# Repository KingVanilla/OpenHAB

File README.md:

# OpenHAB
This repository contains configuration files for my OpenHAB2 home automation system.

Included in this repository are details about my custom alarm system which integrates the ESP32/ESP8266 chipset with OpenHAB.  Included information contains all hardware and software schematics.

## How it all works
My family has several [Bravo5 motion detectors](http://www.dsc.com/alarm-security-products/BV-500GB,%20BV-501GB,%20BV-502GB%20-%20Bravo%C2%AE%205%20360%C2%B0%20Ceiling-Mount%20PIR%20Motion%20Detectors/76) in our home which were prevoisly interfaced with a standard unmonitored alarm system.  4-conductor cabling was ran from each sensor to the control board as well as to 2 keypads on the main and second floor of our home.  The 4-conductor cable delivers 12V to each sensor with a pair of wires.  The remaining pair of wires is connected to the internal relay contact of the motion sensor which are electrically connected by the relay when motion is detected.  I have these sensors interfaced with my ESP8266 via optocouplers so that the 12V signal from the sensor does not fry the ESP which operates on 3.3V.  To replace the 2 keypads in our home I opted to use Amazon Fire tablets and HABPanel.  This solution proves cost-effective, simple to impliment, and elegant.  I used to 4-conductor cable going to these locations to pass 12V to these [USB charging adapters](https://smile.amazon.com/gp/product/B07121W7Q4/ref=oh_aui_search_detailpage?ie=UTF8&psc=1) to keep the tablets supplied with a charge.  I followed [this guide on YouTube](https://www.youtube.com/watch?v=DBfwKYFbbb8) to get the tablets running the HABPanel interface.  Beware, however, that Fire tablets don't allow you to unlock them via Tasker which basically means that you can't have the tablets automatically lock and unlock when there's motion.  I just have mine setup so that the screen is contantly on and never locks. The system logic occurs on the OpenHAB side, so the ESP8266 is simply reporting motion to OpenHAB and receiving commands when to trigger the siren relay.  Connected to the siren relay is this [Elk siren driver board](https://www.homecontrols.com/ELK-Two-Channel-Siren-Driver-Module-ELK101) which has a "chirp" and "constant" tone setting.

## HABPanel
- The passcode input is interfaced though the "Universal Keypad widget" which I have linked to the alarmKeypadInput item 
- Several "Attention with Button" widgets display the alarm status and zone status for each sensor.  
- "Selection" widiget with "Arm=Arm,Chime=Chime,Triggered=Manual Trip" as my list of comma-separated choices to control the alarm mode
- Button to control the lights on the main level of my home
- Button and "Attention with Button" to control and display the status of my garage  

## My PCB design files
The PCB files in this repository feature a board which can interface with up to 4 motion sensors and 1 relay.  The board takes a 12V 5A power supply via a standard DC power-jack.  The design features 4 M3 mounting holes, 1 power LED connected to the 3.3V line, 1 LED connected to D5, and a screw-terminal connected to 12V which I have used to connect to the 4-conductor cabling to run power to the tablets.  You can, obviously, modify the design to meet your own specifications.

## BOM for PCB (links to DigiKey and AmazonSmile)
For the PCB itself you will need:
 - [1x DC Jack](https://www.digikey.com/product-detail/en/cui-inc/PJ-102AH/CP-102AH-ND/408448)
 - [Non-stackable female headers](https://smile.amazon.com/Straight-Female-Header-Spacing-Connector/dp/B00TGOJE1W/ref=sr_1_7?ie=UTF8&qid=1528657475&sr=8-7&keywords=female+headers)
 - [1x ESP8266](https://smile.amazon.com/HiLetgo-Internet-Development-Wireless-Micropython/dp/B010O1G1ES/ref=sr_1_1_sspa?s=electronics&ie=UTF8&qid=1528657504&sr=1-1-spons&keywords=esp8266&psc=1)
 - [1x 2-pin 3.5mm screw terminal](https://www.digikey.com/product-detail/en/phoenix-contact/1984617/277-1721-ND/950849)
 - [1x 12V to 5V regulator](https://smile.amazon.com/DROK-Regulator-Converter-Step-down-Transformer/dp/B0758ZTS61/ref=sr_1_10?ie=UTF8&qid=1528657574&sr=8-10&keywords=12v+to+5v+converter)
 - [2x 68 ohm 0603 resistors](https://www.digikey.com/product-detail/en/rohm-semiconductor/ESR03EZPJ270/RHM27DCT-ND/4053754)
 - [2x 0805 leds](https://www.digikey.com/product-detail/en/lite-on-inc/LTST-C170KFKT/160-1413-1-ND/386774)

For each sensor you wish to interface with you will need:
 - [1x PCB screw terminal connector](https://smile.amazon.com/gp/product/B01M5FARN8/ref=oh_aui_search_detailpage?ie=UTF8&psc=1)
 - [1x PC817 optocoupler](https://smile.amazon.com/gp/product/B06X6M2NNY/ref=oh_aui_search_detailpage?ie=UTF8&psc=1)
 - [1x 0603 10k ohm resistor](https://www.digikey.com/product-detail/en/rohm-semiconductor/ESR03EZPJ103/RHM10KDCT-ND/1762925)
 - [1x 0603 1k ohm resistor](https://www.digikey.com/product-detail/en/rohm-semiconductor/ESR03EZPF1001/RHM1.00KADCT-ND/1983752)
 - [1x RB715S SMD diode](https://www.digikey.com/product-detail/en/rohm-semiconductor/RB751S-40TE61/RB751S-40TE61CT-ND/650794)
 
For each relay trigger you wish to interface with you will need:
 - [1x PC817 optocoupler](https://smile.amazon.com/gp/product/B06X6M2NNY/ref=oh_aui_search_detailpage?ie=UTF8&psc=1)
 - [2x 0603 100 resistor](https://www.digikey.com/product-detail/en/rohm-semiconductor/ESR03EZPJ101/RHM100DCT-ND/1983776)
 - [1x RB715S SMD diode](https://www.digikey.com/product-detail/en/rohm-semiconductor/RB751S-40TE61/RB751S-40TE61CT-ND/650794)
 - [1x 2N3904 transistor](https://smile.amazon.com/gp/product/B008IFYBWW/ref=oh_aui_search_detailpage?ie=UTF8&psc=1)
 - [1x relay](https://www.digikey.com/product-detail/en/omron-electronics-inc-emc-div/G5LE-1-DC5/Z1014-ND/280368)
 - [1x 2-pin 3.5mm screw terminal](https://www.digikey.com/product-detail/en/phoenix-contact/1984617/277-1721-ND/950849)

## How to make custom sound effects: 
In my my alarmController.rules file you may have noticed that I have several sound files which I reference.  These files are contained within my "sounds" folder in my OpenHAB configuration on my Raspberry Pi.  These files are a combination of sound effects I complied using a YouTube to MP3 converter and [Siri text-to-speech using the "say" function](https://www.lifewire.com/mac-say-command-with-talking-terminal-2260772) through Terminal on my Mac.  I cannot upload the sound files here due to copyright restrictions, however, you would likely want to make your own custom sound effects anyways.  Here are what mine are:  
- chime.mp3 - A mellow single-tone "blip" noise  
- incorrect.mp3 - Agressive error noise  
- armed.mp3 - A mellow 2-tone "bing" noise followed by "Hello, system is armed"  
- welcome.mp3 - A mellow 2-tone "bing" noise followed by "Hello, system disarmed"  
- alarm triggered.mp3 - "Danger" followed by agressive siren alert tone

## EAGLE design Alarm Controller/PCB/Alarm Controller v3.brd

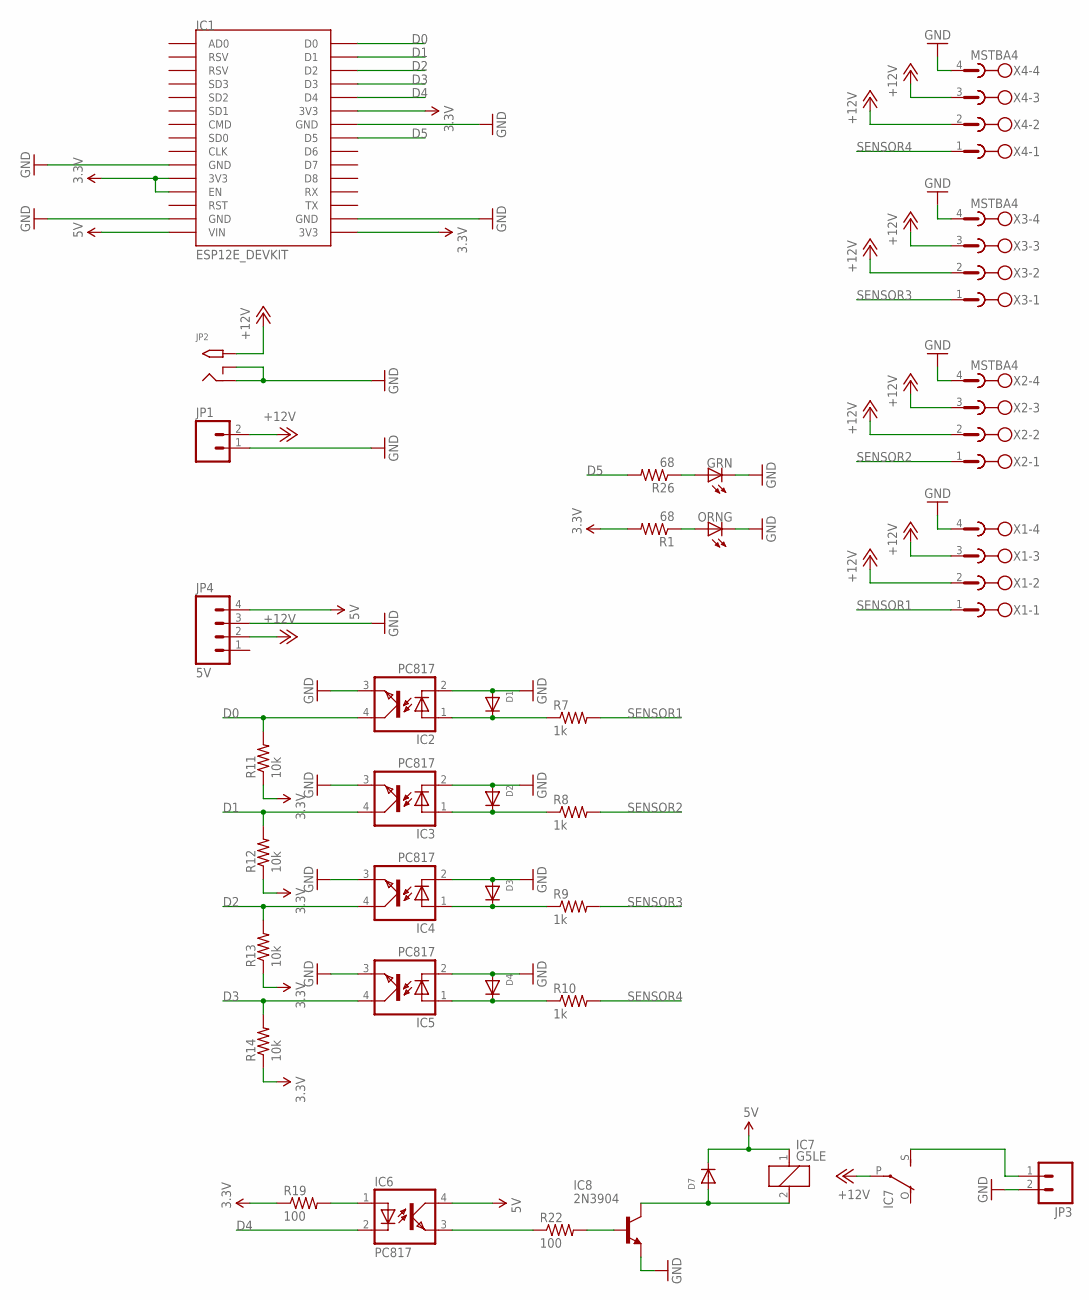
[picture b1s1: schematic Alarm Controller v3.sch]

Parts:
D1, D2, D3, D4, D7: RB751S-40TE61CT-ND; SOD-523
IC1: ESP12E_DEVKIT
IC2, IC3, IC4, IC5, IC6: PC817; DIL04
IC7: G5LE
IC8: 2N3904; TO92
JP1, JP3: M023.5MM_LOCK; SCREWTERMINAL-3.5MM-2_LOCK
JP2: 2.1MMJACKTHM; PJ-102A
JP4: 5V; 1X04_LOCK_LONGPADS
LED: GRN; SML0805
LED2: ORNG; SML0805
R1, R26: 68; 0603-RES
R7, R8, R9, R10: 1k; 0603-RES
R11, R12, R13, R14: 10k; 0603-RES
R19, R22: 100; 0603-RES
X1, X2, X3, X4: MSTBA4

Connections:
3.3V: IC1.3V3@0 (3V3), IC1.3V3@1 (3V3), IC1.3V3@2 (3V3), IC1.EN, R1.2, R11.1, R12.1, R13.1, R14.1, R19.1
5V: D7.K (C), IC1.VIN, IC6.4 (COL), IC7.1, JP4.4
+12V: IC7.P, JP1.2, JP2.TIP, JP4.2, X1.2, X1.3, X2.2, X2.3, X3.2, X3.3, X4.2, X4.3
D0: IC1.D0, IC2.4 (COL), R11.2
D1: IC1.D1, IC3.4 (COL), R12.2
D2: IC1.D2, IC4.4 (COL), R13.2
D3: IC1.D3, IC5.4 (COL), R14.2
D4: IC1.D4, IC6.2 (C)
D5: IC1.D5, R26.2
GND: D1.A, D2.A, D3.A, D4.A, IC1.GND@0 (GND), IC1.GND@1 (GND), IC1.GND@2 (GND), IC1.GND@3 (GND), IC2.2 (C), IC2.3 (EMIT), IC3.2 (C), IC3.3 (EMIT), IC4.2 (C), IC4.3 (EMIT), IC5.2 (C), IC5.3 (EMIT), IC8.3 (E), JP1.1, JP2.RING, JP2.RING_SW, JP3.2, JP4.3, LED.C, LED2.C, X1.4, X2.4, X3.4, X4.4
unnamed: LED2.A, R1.1
unnamed: D7.A, IC7.2, IC8.1 (C)
unnamed: D1.K (C), IC2.1 (A), R7.1
unnamed: D2.K (C), IC3.1 (A), R8.1
unnamed: D3.K (C), IC4.1 (A), R9.1
unnamed: D4.K (C), IC5.1 (A), R10.1
unnamed: IC6.1 (A), R19.2
unnamed: IC6.3 (EMIT), R22.1
unnamed: IC8.2 (B), R22.2
unnamed: IC7.S, JP3.1
unnamed: LED.A, R26.1
SENSOR1: R7.2, X1.1
SENSOR2: R8.2, X2.1
SENSOR3: R9.2, X3.1
SENSOR4: R10.2, X4.1

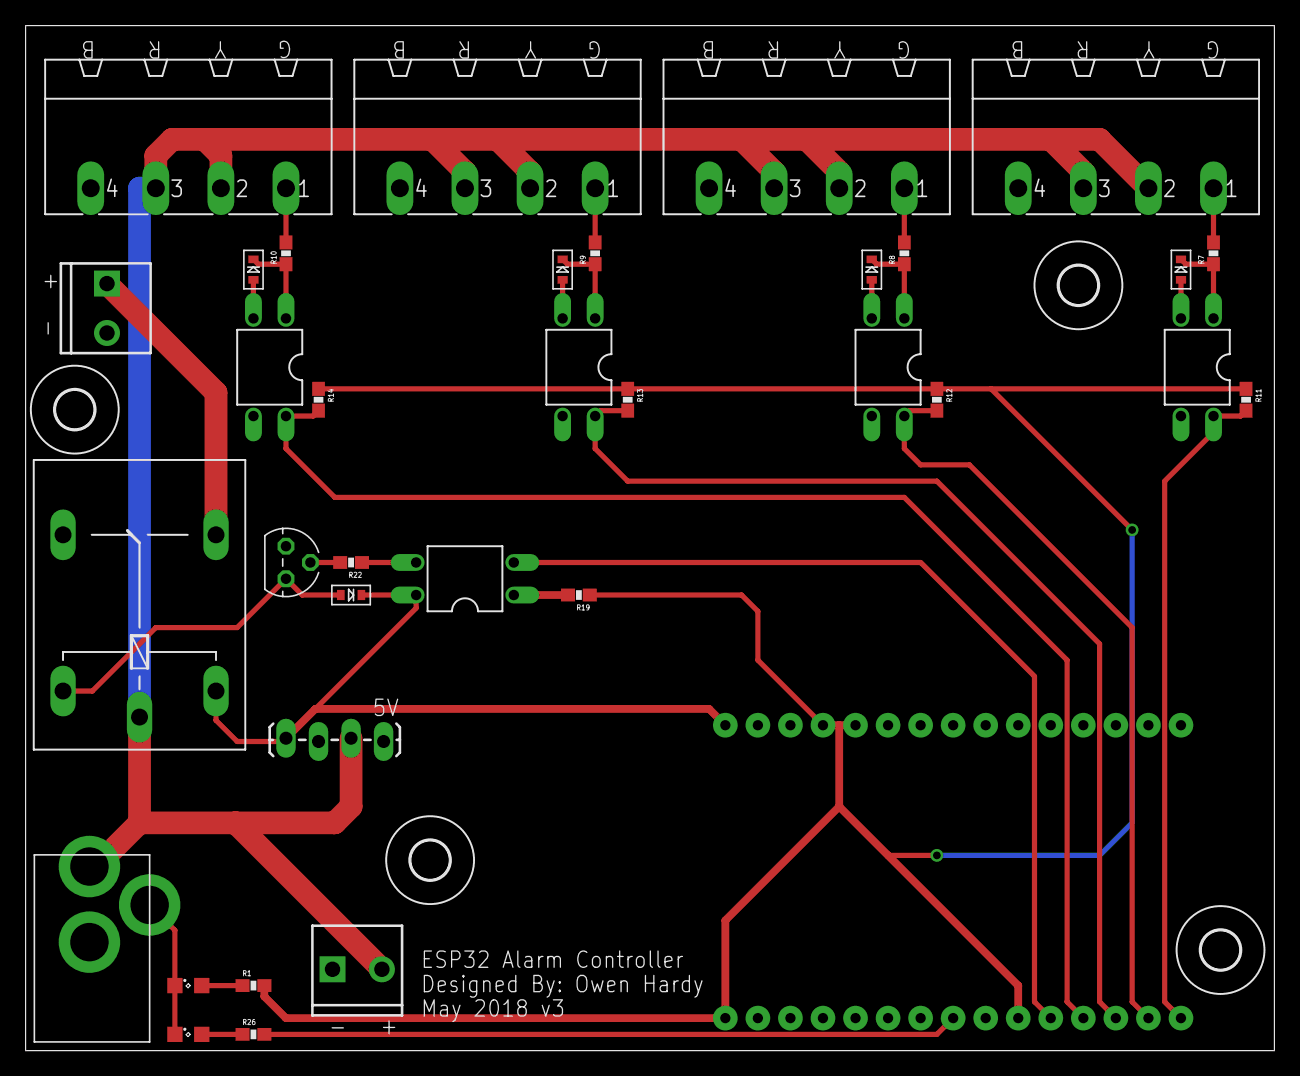
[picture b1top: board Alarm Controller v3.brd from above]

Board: 2 copper layers, 97.5 x 80.0 mm, 39 parts (0 on the bottom side), 25 nets.

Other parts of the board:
U$4, U$5, U$6, U$9: 3,0

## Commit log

2018-06-10 Create empty
2018-06-10 Rename Alarm Controller/README.md to README.md
2018-06-10 Rename alarmController.ino to Alarm Controller/alarmController.ino
2018-06-10 Rename alarmController.items to Alarm Controller/alarmController.items
2018-06-10 Rename alarmController.rules to Alarm Controller/alarmController.rules
2018-06-10 Create blank
2018-06-10 Rename Alarm Controller/alarmController.items to Alarm Controller/OpenHAB Config/alarmController.items
2018-06-10 Rename Alarm Controller/alarmController.rules to Alarm Controller/OpenHAB Config/alarmController.rules

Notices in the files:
parts and their libraries:
SparkFun-Connectors: Licensing: CC v3.0 Share-Alike You are welcome to use this library for commercial purposes.
